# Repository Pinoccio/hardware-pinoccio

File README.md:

pinoccio-hardware-reference
===========================

Contained are the schematics, board layout, data sheets, and BOM for the
Pinoccio board. The firmware directory also has code for the 16u2 chip
on the board and the booloader running in the main MCU.

For the firmware, the branches contain only the source files. The
compiled versions used in production can be found in the tagged
revisions only.

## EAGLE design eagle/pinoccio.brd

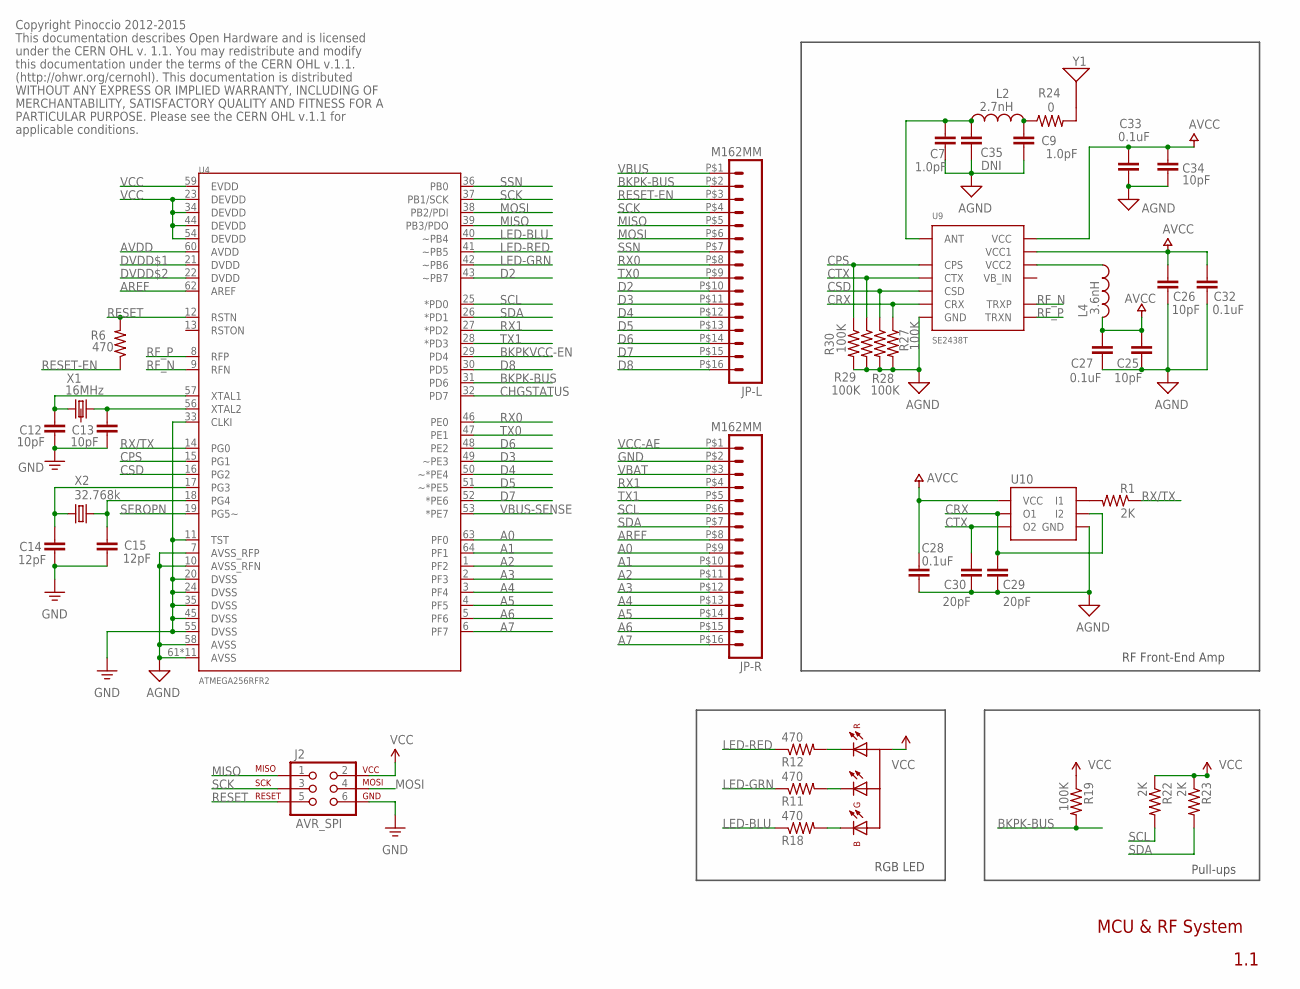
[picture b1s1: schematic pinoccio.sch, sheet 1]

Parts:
C7, C9: 1.0pF; 0402-CAP
C12, C13, C25, C26, C34: 10pF; 0402-CAP
C14, C15: 12pF; 0402-CAP
C27, C28, C32, C33: 0.1uF; 0402-CAP
C29, C30: 20pF; 0402-CAP
C35: DNI; 0402-CAP
J2: AVR_SPI; 2X3-PAD
JP-L: M162MM; 1X16_2MM
JP-R: M162MM; 1X16_2MM
L2: 2.7nH; 0402
L4: 3.6nH; 0402
R1, R22, R23: 2K; 0402-RES
R6, R11, R12, R18: 470; 0402-RES
R19, R27, R28, R29, R30: 100K; 0402-RES
R24: 0; 0402-RES
U4: ATMEGA256RFR2; QFN-64-256RFR2
U8: LED-RGB; PLCC4
U9: SE2438T; QFN-20-SE2438T
U10: INVERTER-DUALPAK; MICROPAK
X1: 16MHz; CRYSTAL-SMD-2.5X2-ABM10
X2: 32.768k; CRYSTAL-SMD-2X1.2-ABS06
Y1: ANTENNA2SMD5; ANTENNA-CHIP5

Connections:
A0: JP-R.P$9 (9), U4.63 (PF0)
A1: JP-R.P$10 (10), U4.64 (PF1)
A2: JP-R.P$11 (11), U4.1 (PF2)
A3: JP-R.P$12 (12), U4.2 (PF3)
A4: JP-R.P$13 (13), U4.3 (PF4)
A5: JP-R.P$14 (14), U4.4 (PF5)
A6: JP-R.P$15 (15), U4.5 (PF6)
A7: JP-R.P$16 (16), U4.6 (PF7)
ANT: C7.1, C35.1, L2.2, U9.13 (ANT)
AREF: JP-R.P$8 (8), U4.62 (AREF)
AVDD: U4.60 (AVDD); also elsewhere on the board
BKPK-BUS: JP-L.P$2 (2), R19.2, U4.31 (PD6)
BKPKVCC-EN: U4.29 (PD4); also elsewhere on the board
CHGSTATUS: U4.32 (PD7); also elsewhere on the board
CPS: R30.1, U4.15 (PG1), U9.8 (CPS)
CRX: C29.1, R27.1, U9.10 (CRX), U10.P$3 (I2), U10.P$6 (O1)
CSD: R28.1, U4.16 (PG2), U9.12 (CSD)
CTX: C30.1, R29.1, U9.11 (CTX), U10.P$4 (O2)
D2: JP-L.P$10 (10), U4.43 (~PB7)
D3: JP-L.P$11 (11), U4.49 (~PE3)
D4: JP-L.P$12 (12), U4.50 (~*PE4)
D5: JP-L.P$13 (13), U4.51 (~*PE5)
D6: JP-L.P$14 (14), U4.48 (PE2)
D7: JP-L.P$15 (15), U4.52 (*PE6)
D8: JP-L.P$16 (16), U4.30 (PD5)
DVDD$1: U4.21 (DVDD); also elsewhere on the board
DVDD$2: U4.22 (DVDD); also elsewhere on the board
GND: C7.2, C9.2, C12.2, C13.2, C14.2, C15.2, C25.2, C26.2, C27.2, C28.2, C29.2, C30.2, C32.2, C33.2, C34.2, C35.2, J2.6, JP-R.P$2 (2), R27.2, R28.2, R29.2, R30.2, U4.7 (AVSS_RFP), U4.10 (AVSS_RFN), U4.11 (TST), U4.20 (DVSS), U4.24 (DVSS), U4.33 (CLKI), U4.35 (DVSS), U4.45 (DVSS), U4.55 (DVSS), U4.58 (AVSS), U4.61 (AVSS), U4.GND$1 (AVSS), U4.GND$2 (AVSS), U4.GND$3 (AVSS), U4.GND$4 (AVSS), U4.GND$5 (AVSS), U4.GND$6 (AVSS), U4.GND$7 (AVSS), U4.GND$8 (AVSS), U4.GND$9 (AVSS), U4.PADDLE (AVSS), U9.5 (GND), U9.14 (GND), U9.18 (GND), U9.20 (GND), U9.EP (GND), U9.GND, U9.GND$1 (GND), U10.P$2 (GND); also elsewhere on the board
LED-BLU: R18.1, U4.40 (~PB4)
LED-GRN: R11.1, U4.42 (~PB6)
LED-RED: R12.1, U4.41 (~PB5)
MISO: J2.1, JP-L.P$5 (5), U4.39 (PB3/PDO)
MOSI: J2.4, JP-L.P$6 (6), U4.38 (PB2/PDI)
unnamed: R12.2, U8.P$1 (R-C)
unnamed: L4.2, U9.19 (VCC2)
unnamed: R11.2, U8.P$4 (G-C)
unnamed: R18.2, U8.P$3 (B-C)
unnamed: R1.2, U10.P$1 (I1)
unnamed: C14.1, U4.17 (PG3), X2.P$1 (1)
unnamed: C15.1, U4.18 (PG4), X2.P$2 (2)
unnamed: C9.1, L2.1, R24.1
unnamed: R24.2, Y1.FEED
RESET: J2.5, R6.2, U4.12 (RSTN); also elsewhere on the board
RESET-EN: JP-L.P$3 (3), R6.1
RF_N: U4.9 (RFN), U9.3 (TRXP)
RF_P: U4.8 (RFP), U9.4 (TRXN)
RX0: JP-L.P$8 (8), U4.46 (PE0); also elsewhere on the board
RX1: JP-R.P$4 (4), U4.27 (*PD2)
RX/TX: R1.1, U4.14 (PG0)
SCK: J2.3, JP-L.P$4 (4), U4.37 (PB1/SCK)
SCL: JP-R.P$6 (6), R22.2, U4.25 (*PD0); also elsewhere on the board
SDA: JP-R.P$7 (7), R23.2, U4.26 (*PD1); also elsewhere on the board
SEROPN: U4.19 (PG5~); also elsewhere on the board
SSN: JP-L.P$7 (7), U4.36 (PB0)
TX0: JP-L.P$9 (9), U4.47 (PE1); also elsewhere on the board
TX1: JP-R.P$5 (5), U4.28 (*PD3)
VBAT: JP-R.P$3 (3); also elsewhere on the board
VBUS: JP-L.P$1 (1); also elsewhere on the board
VBUS-SENSE: U4.53 (*PE7); also elsewhere on the board
VCC: C25.1, C26.1, C27.1, C28.1, C32.1, C33.1, C34.1, J2.2, L4.1, R19.1, R22.1, R23.1, U4.23 (DEVDD), U4.34 (DEVDD), U4.44 (DEVDD), U4.54 (DEVDD), U4.59 (EVDD), U8.P$2 (A), U9.1 (VCC1), U9.6 (VCC), U10.P$5 (VCC); also elsewhere on the board
VCC-AE: JP-R.P$1 (1); also elsewhere on the board
X1_N: C13.1, U4.56 (XTAL2), X1.P$3 (2)
X1_P: C12.1, U4.57 (XTAL1), X1.P$1 (1)

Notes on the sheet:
1.1
Copyright Pinoccio 2012-2015
This documentation describes Open Hardware and is licensed
under the CERN OHL v. 1.1. You may redistribute and modify
this documentation under the terms of the CERN OHL v.1.1.
(http://ohwr.org/cernohl). This documentation is distributed
WITHOUT ANY EXPRESS OR IMPLIED WARRANTY, INCLUDING OF
MERCHANTABILITY, SATISFACTORY QUALITY AND FITNESS FOR A
PARTICULAR PURPOSE. Please see the CERN OHL v.1.1 for
applicable conditions.
MCU & RF System
Pull-ups
RF Front-End Amp
RGB LED

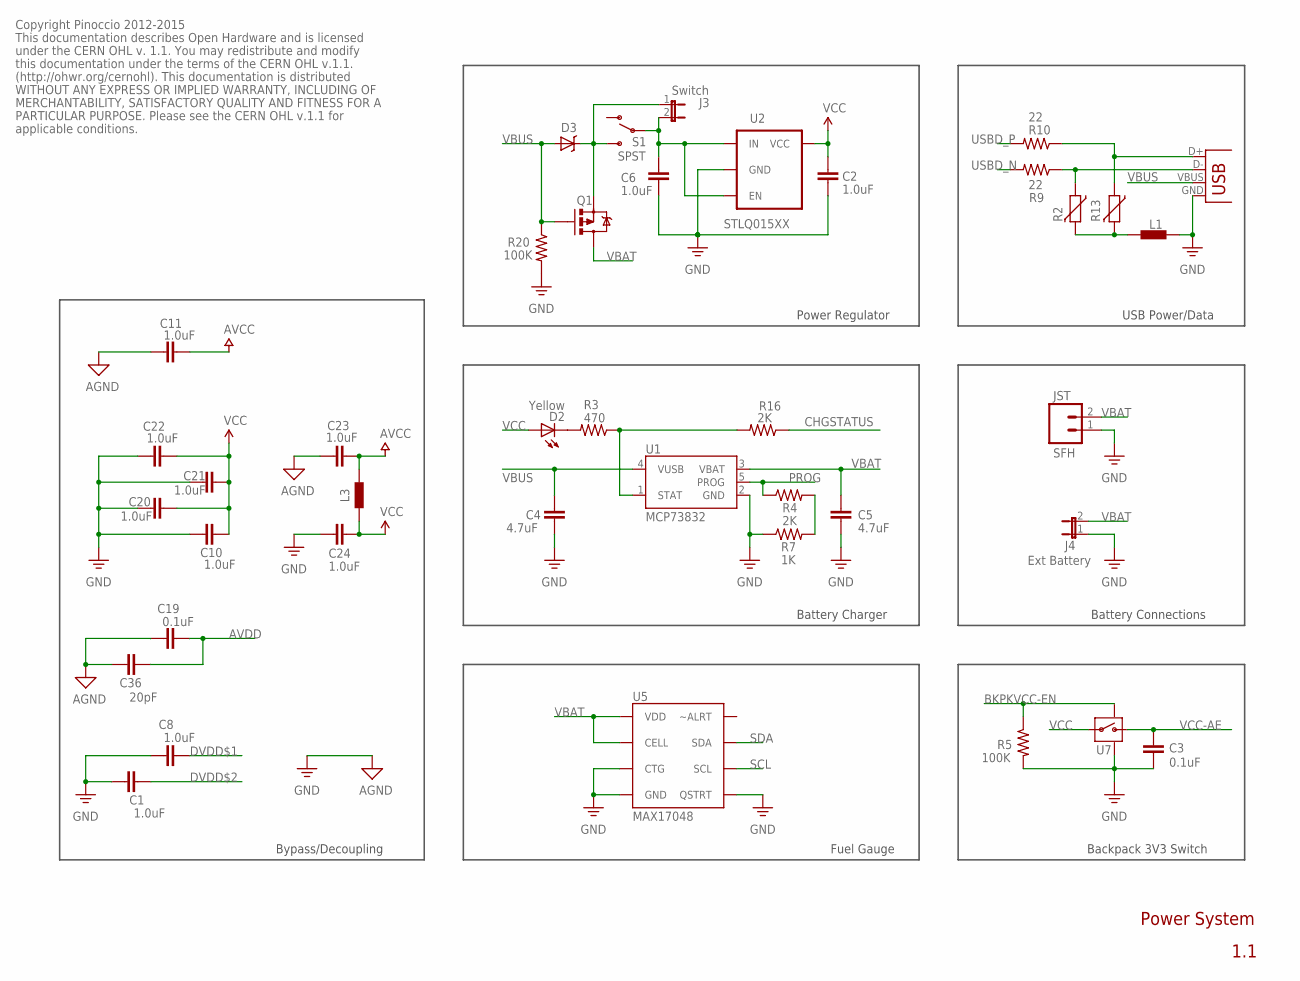
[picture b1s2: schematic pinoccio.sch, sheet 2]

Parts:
C1, C2, C6, C8, C10, C11, C20, C21, C22, C23, C24: 1.0uF; 0402-CAP
C3, C19: 0.1uF; 0402-CAP
C4, C5: 4.7uF; 0402-CAP
C36: 20pF; 0402-CAP
D2: Yellow; LED-0603
D3: DIODE-SCHOTTKY; 0603-DIODE
J3: Switch; 1X02
J4: Ext Battery; 1X02
JST: SFH; JST-SFH
L1, L3: BEAD; 0603
Q1: PFET; SOT23-3
R2, R13: VAR; 0402
R3: 470; 0402-RES
R4, R16: 2K; 0402-RES
R5, R20: 100K; 0402-RES
R7: 1K; 0402-RES
R9, R10: 22; 0402-RES
S1: SPST; SWITCH-SPDT-SMD
U1: MCP73832; SOT23-5
U2: STLQ015XX; SOT666
U5: MAX17048; DFN-8
U7: SWITCH; TDFN4
USB-JACK: USB-MICROB

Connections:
AVDD: C19.1, C36.1; also elsewhere on the board
BKPKVCC-EN: R5.1, U7.P$4 (ON); also elsewhere on the board
CHGSTATUS: R16.1; also elsewhere on the board
DVDD$1: C8.1; also elsewhere on the board
DVDD$2: C1.1; also elsewhere on the board
GND: C1.2, C2.2, C3.2, C4.2, C5.2, C6.2, C8.2, C10.2, C11.2, C19.2, C20.2, C21.2, C22.2, C23.2, C24.2, C36.2, J4.1, JST.1, L1.1, R5.2, R7.1, R20.2, U1.2 (GND), U2.P$2 (GND), U5.P$1 (CTG), U5.P$4 (GND), U5.P$6 (QSTRT), U5.P$9 (GND), U7.P$2 (GND), U7.P$5 (GND), USB-JACK.GND; also elsewhere on the board
unnamed: R4.2, R7.2
unnamed: L1.2, R2.2, R13.2
unnamed: R3.1, R16.2, U1.1 (STAT)
unnamed: D2.C, R3.2
unnamed: D3.C, J3.1, Q1.2 (S), S1.3 (S)
PROG: R4.1, U1.5 (PROG); also elsewhere on the board
SCL: U5.P$7 (SCL); also elsewhere on the board
SDA: U5.P$8 (SDA); also elsewhere on the board
USBDIN_N: R2.1, R9.1, USB-JACK.D-
USBDIN_P: R10.1, R13.1, USB-JACK.D+
USBD_N: R9.2; also elsewhere on the board
USBD_P: R10.2; also elsewhere on the board
VBAT: C5.1, J4.2, JST.2, Q1.3 (D), U1.3 (VBAT), U5.P$2 (CELL), U5.P$3 (VDD); also elsewhere on the board
VBUS: C4.1, D3.A, Q1.1 (G), R20.1, U1.4 (VUSB), USB-JACK.VBUS; also elsewhere on the board
VCC: C2.1, C10.1, C11.1, C20.1, C21.1, C22.1, C23.1, C24.1, D2.A, L3.1, L3.2, U2.P$4 (VCC), U7.P$3 (IN); also elsewhere on the board
VCC-AE: C3.1, U7.P$1 (OUT); also elsewhere on the board
VIN: C6.1, J3.2, S1.2, U2.P$1 (EN), U2.P$3 (IN)

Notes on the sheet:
1.1
Power Regulator
Battery Charger
Fuel Gauge
Bypass/Decoupling
USB Power/Data
Battery Connections
Backpack 3V3 Switch
Power System
Copyright Pinoccio 2012-2015
This documentation describes Open Hardware and is licensed
under the CERN OHL v. 1.1. You may redistribute and modify
this documentation under the terms of the CERN OHL v.1.1.
(http://ohwr.org/cernohl). This documentation is distributed
WITHOUT ANY EXPRESS OR IMPLIED WARRANTY, INCLUDING OF
MERCHANTABILITY, SATISFACTORY QUALITY AND FITNESS FOR A
PARTICULAR PURPOSE. Please see the CERN OHL v.1.1 for
applicable conditions.

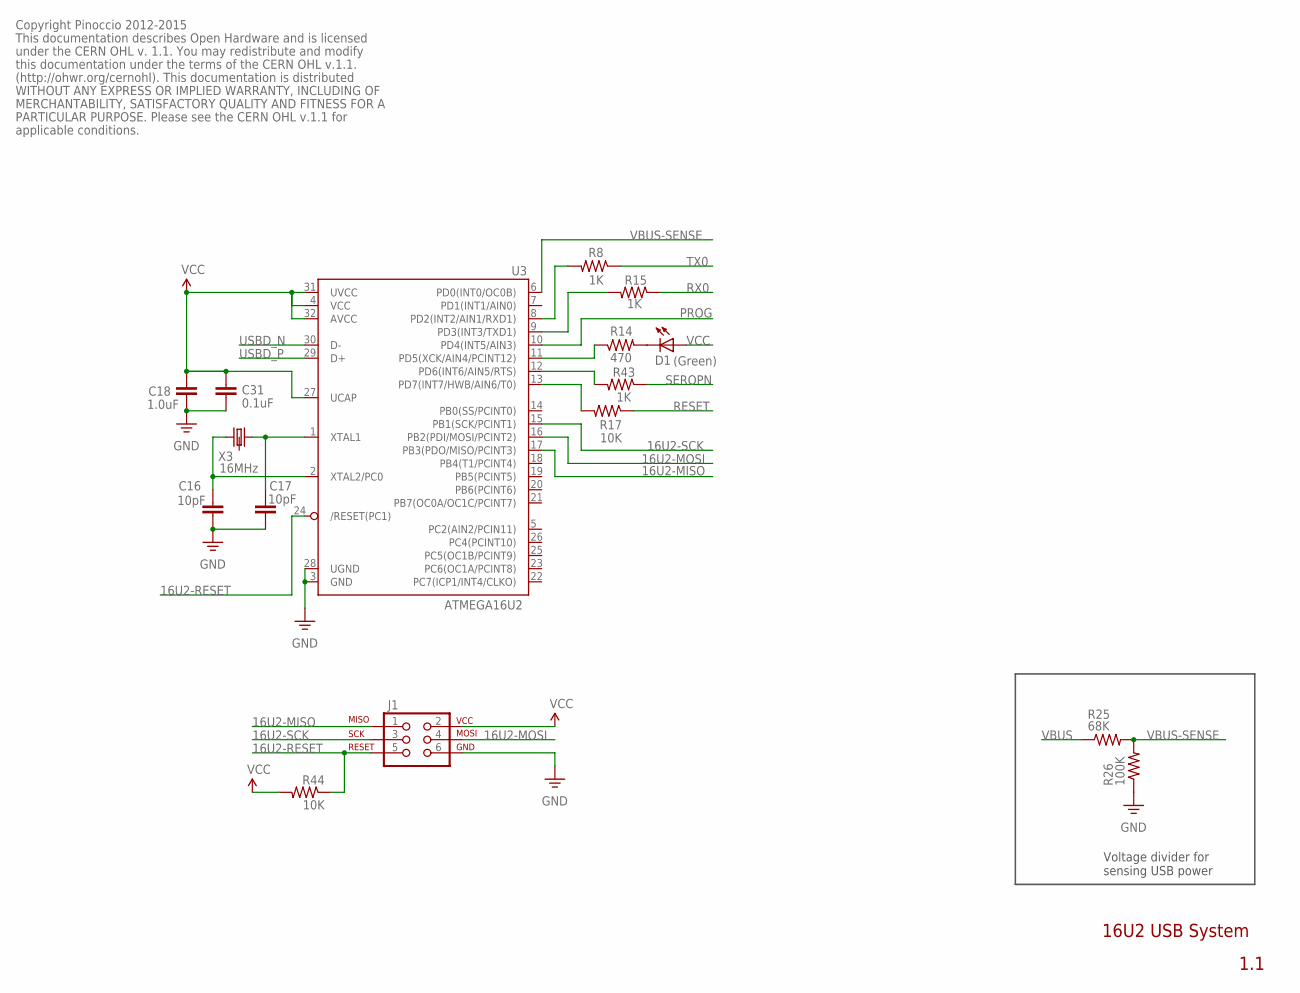
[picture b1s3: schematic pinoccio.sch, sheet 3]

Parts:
C16, C17: 10pF; 0402-CAP
C18: 1.0uF; 0402-CAP
C31: 0.1uF; 0402-CAP
D1: (Green); LED-0603
J1: AVR_SPI_PRG_6; 2X3-PAD
R8, R15, R43: 1K; 0402-RES
R14: 470; 0402-RES
R17, R44: 10K; 0402-RES
R25: 68K; 0402-RES
R26: 100K; 0402-RES
U3: ATMEGA16U2; QFN-32
X3: 16MHz; CRYSTAL-SMD-2.5X2-ABM10

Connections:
16U2-MISO: J1.1, U3.17 (PB3(PDO/MISO/PCINT3))
16U2-MOSI: J1.4, U3.16 (PB2(PDI/MOSI/PCINT2))
16U2-RESET: J1.5, R44.1, U3.24 (/RESET(PC1))
16U2-SCK: J1.3, U3.15 (PB1(SCK/PCINT1))
GND: C16.2, C17.2, C18.2, C31.2, J1.6, R26.1, U3.3 (GND), U3.28 (UGND); also elsewhere on the board
unnamed: R43.2, U3.12 (PD6(INT6/AIN5/RTS))
unnamed: R17.2, U3.13 (PD7(INT7/HWB/AIN6/T0))
unnamed: R15.2, U3.9 (PD3(INT3/TXD1))
unnamed: R8.2, U3.8 (PD2(INT2/AIN1/RXD1))
unnamed: R14.1, U3.11 (PD5(XCK/AIN4/PCINT12))
unnamed: D1.C, R14.2
PROG: U3.10 (PD4(INT5/AIN3)); also elsewhere on the board
RESET: R17.1; also elsewhere on the board
RX0: R15.1; also elsewhere on the board
SEROPN: R43.1; also elsewhere on the board
TX0: R8.1; also elsewhere on the board
USBD_N: U3.30 (D-); also elsewhere on the board
USBD_P: U3.29 (D+); also elsewhere on the board
VBUS: R25.1; also elsewhere on the board
VBUS-SENSE: R25.2, R26.2, U3.6 (PD0(INT0/OC0B)); also elsewhere on the board
VCC: C18.1, C31.1, D1.A, J1.2, R44.2, U3.4 (VCC), U3.27 (UCAP), U3.31 (UVCC), U3.32 (AVCC); also elsewhere on the board
X3_N: C16.1, U3.2 (XTAL2/PC0), X3.P$1 (1)
X3_P: C17.1, U3.1 (XTAL1), X3.P$3 (2)

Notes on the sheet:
1.1
16U2 USB System
Voltage divider for sensing USB power
Copyright Pinoccio 2012-2015
This documentation describes Open Hardware and is licensed
under the CERN OHL v. 1.1. You may redistribute and modify
this documentation under the terms of the CERN OHL v.1.1.
(http://ohwr.org/cernohl). This documentation is distributed
WITHOUT ANY EXPRESS OR IMPLIED WARRANTY, INCLUDING OF
MERCHANTABILITY, SATISFACTORY QUALITY AND FITNESS FOR A
PARTICULAR PURPOSE. Please see the CERN OHL v.1.1 for
applicable conditions.

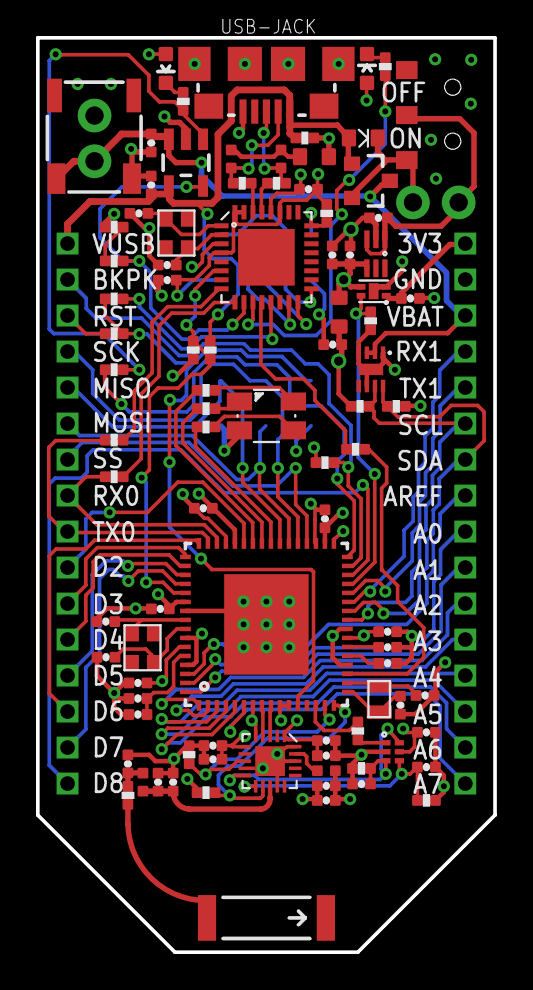
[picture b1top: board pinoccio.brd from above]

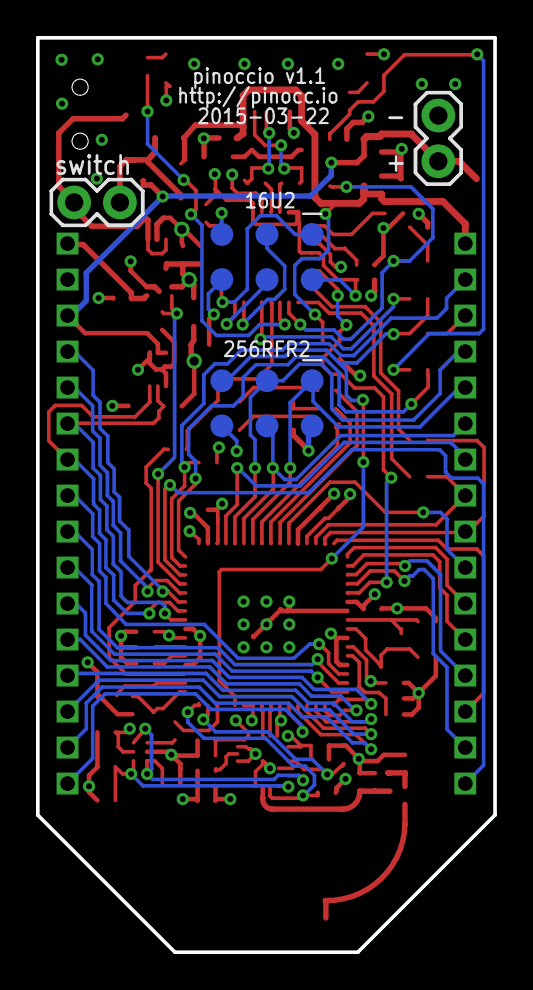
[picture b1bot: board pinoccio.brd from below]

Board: 4 copper layers, 25.4 x 50.8 mm, 97 parts (4 on the bottom side), 86 nets.

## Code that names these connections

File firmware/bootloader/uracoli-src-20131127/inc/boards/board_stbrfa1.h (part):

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<pre>
RCB2xx        | Pin           | RCB128RFA1   | Remark
------------------------------------------------------------------
PA0             EXT1.23         PB0          \
PA1             EXT1.24         PB1          |  This is the
PA2             EXT1.25         PB2          |  multiplexed
PA3             EXT1.26         PB3          >  data/low address
PA4             EXT1.27         PB4          |  bus of the classic
PA5             EXT1.28         PB5          |  XMEM interface
PA6             EXT1.29         PB6          |
PA7             EXT1.30         PB7          /
PE4             EXT1.6          RSTON        Reset output
PE5             EXT1.5          TST          Used for "HV" prog
PC4             EXT0.25         PD4          \  Matches A12...A15
PC5             EXT0.26         PD5          |  of normal address bus;
PC6             EXT0.27         PD6          >  used to distinguish
PC7             EXT0.28         PD7          /  FTDI vs. LED vs. button
PG0             EXT0.17         PE4          xmem /WR
PG1             EXT0.18         PE5          xmem /RD
PB6             EXT0.1          PG0          GPIO
PB7             EXT0.2          PG1          GPIO
XTAL1           EXT0.7          CLKI
</pre>
    In addition, the standard STB pin mapping is retained for:

    PE7  FT245 /RXF
    PE6  FT245 /TXE
    PG2  ALE

    The STBxxx has memory mapped LEDS and Keys.
    KEY: memory mapped on external memory bus address 0x4000
    LEDS
     - 2 x memory mapped at 0x4000  (Option 1)
     - 3 x IO mapped at PE2:PE4 (Option 2)


    You can select between using the LEDs on the RCB or on the STB.
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    DDRD |= 0xc0;               /* xmem A14...A15 */
    PORTD = (PORTD & ~0xc0) | 0x80; /* high addr 0x80 => external
                                     * SRAM */
    PORTE &= ~0x10;             /* PE4: xmem /WR, activate to make the
                                 * 74VHC245MTC not drive the bus */
    PORTE |= 0x20;              /* PE5: xmem /RD, deactivate */
    DDRE |= 0x30;               /* make /RD and /WR outputs */
    PORTG &= ~0x04;             /* PG2: xmem ALE; not used but keep
                                 * low all the time */
    DDRG |= 0x04;
}
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
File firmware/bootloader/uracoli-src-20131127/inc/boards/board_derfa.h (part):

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

radiofaro:
  LEDS: PG1, PG2

</pre>

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
#define LED_INIT() \
    do {\
        DDRB |= (_BV(PB0) | _BV(PB1) | _BV(PB2) | _BV(PB3));\
        PORTB |= (_BV(PB0) | _BV(PB1) | _BV(PB2) | _BV(PB3));\
    } while(0)


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#if BOARD_TYPE == BOARD_DERFN128

    /*
     * USBRD = Pin27 = PD2
     * USBWR = Pin10 = PD3
     * RXF   = Pin30 = PE2
     * TXE   = Pin21 = PB5
     * Data Port:
     * D0 =  Pin16 = PB0
     * D1 =  Pin41 = PF2
     * D2 =  Pin12 = PD5
     * D3 =  Pin06 = PG2
     * D4 =  Pin37 = PE6
     * D5 =  Pin19 = PB4
     * D6 =  Pin39 = PE7
     * D7 =  Pin18 = PB6
     */

    static inline void hif_mmio_init(void)
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        DDRD |= 0xc0;               /* xmem A14...A15 */
        PORTD = (PORTD & ~0xc0) | 0x80; /* high addr 0x80 => external
                                         * SRAM */
        PORTE &= ~0x10;             /* PE4: xmem /WR, activate to make the
                                     * 74VHC245MTC not drive the bus */
        PORTE |= 0x20;              /* PE5: xmem /RD, deactivate */
        DDRE |= 0x30;               /* make /RD and /WR outputs */
        PORTG &= ~0x04;             /* PG2: xmem ALE; not used but keep
                                     * low all the time */
        DDRG |= 0x04;
    }
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
# define TRX_PA_LNA_INIT() \
        do {\
            PORTD &= ~_BV(PD6);\
            DDRD |= _BV(PD6);\
        } while(0)

# define TRX_TX_PA_EI() do {PORTD |= _BV(PD6);} while(0)
# define TRX_TX_PA_DI() do {PORTD &= ~_BV(PD6);} while(0)
# define TRX_RX_LNA_EI() do {PORTD |= _BV(PD6);} while(0)
# define TRX_RX_LNA_DI() do {PORTD &= ~_BV(PD6);} while(0)
#endif /* BOARD_TYPE == BOARD_RASPBEE || BOARD_TYPE == BOARD_DERFN256U0PA || BOARD_TYPE == BOARD_DERFN128U0 */


#if BOARD_TYPE == BOARD_DERFN128U0 || BOARD_TYPE == BOARD_DERFN128
#define I2C_ENABLE() do{\
        DDRD |= (1<<PD6);\
        PORTD &= ~(1<<PD6);\
    }while(0)

#define ISL29020_ADDR (0x44)
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
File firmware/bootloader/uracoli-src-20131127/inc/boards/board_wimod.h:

/* Copyright (c) 2007 - 2011 Axel Wachtler
   All rights reserved.

   Redistribution and use in source and binary forms, with or without
   modification, are permitted provided that the following conditions
   are met:

   * Redistributions of source code must retain the above copyright
     notice, this list of conditions and the following disclaimer.
   * Redistributions in binary form must reproduce the above copyright
     notice, this list of conditions and the following disclaimer in the
     documentation and/or other materials provided with the distribution.
   * Neither the name of the authors nor the names of its contributors
     may be used to endorse or promote products derived from this software
     without specific prior written permission.

   THIS SOFTWARE IS PROVIDED BY THE COPYRIGHT HOLDERS AND CONTRIBUTORS "AS IS"
   AND ANY EXPRESS OR IMPLIED WARRANTIES, INCLUDING, BUT NOT LIMITED TO, THE
   IMPLIED WARRANTIES OF MERCHANTABILITY AND FITNESS FOR A PARTICULAR PURPOSE
   ARE DISCLAIMED. IN NO EVENT SHALL THE COPYRIGHT OWNER OR CONTRIBUTORS BE
   LIABLE FOR ANY DIRECT, INDIRECT, INCIDENTAL, SPECIAL, EXEMPLARY, OR
   CONSEQUENTIAL DAMAGES (INCLUDING, BUT NOT LIMITED TO, PROCUREMENT OF
   SUBSTITUTE GOODS OR SERVICES; LOSS OF USE, DATA, OR PROFITS; OR BUSINESS
   INTERRUPTION) HOWEVER CAUSED AND ON ANY THEORY OF LIABILITY, WHETHER IN
   CONTRACT, STRICT LIABILITY, OR TORT (INCLUDING NEGLIGENCE OR OTHERWISE)
   ARISING IN ANY WAY OUT OF THE USE OF THIS SOFTWARE, EVEN IF ADVISED OF THE
   POSSIBILITY OF SUCH DAMAGE. */

/* $Id$ */
/**
 * @file
 * @brief IMST GmbH WIMOD w/ mega328 and AT86RF230B.
 *
 * see http://www.mikrocontroller.net/attachment/101618/WiMOD240.jpg

 * The wiring of the radio and the ATmega is shown below.
<pre>
     AVR         RF230
     ---         -----
     PB0    <--  INT / ICP1
     PB1    -->  SLPTR
     PB2    -->  /SEL
     PB3    -->  MOSI
     PB4    <--  MISO
     PB5    -->  SCK

     PB6 intentionally unused for XTAL1
     PB7 intentionally unused for XTAL2


    (T1) PD5   <--  CLKM
         PD6   --> /RST
         PD7   --> TST

    USART:
        PD0 RXD
        PD1 TXD

    LED:  None
    KEY:  None


  IM240A      Mega328  Adapter   EvalBoard
  Pin Name              AB_01
  -----------------------------------------
   8  ADC1    ADC7      X1.12
   9  ADC2    ADC6      X1.14
  12  GPIO1   PC0       X1.15     Button1
  13  GPIO2   PC1       X1.16     Button2
  14  GPIO3   PC2       X1.19     Button3
  15  GPIO4   PC3       X1.18     DSW1
  21  GPIO5   PC5       X2.9
  23  GPIO6   PC4       X2.11

  18  DIO1    PD0       X2.18      UART-RX
  19  DIO2    PD1       X2.15      UART-TX
  20  DIO3    PD2       X2.7       LED4
  24  DIO4    PD3       X2.6       LED3
  25  DIO5    PD4       X2.5       LED2

</pre>

  @par Build Options

 - im240a : AT86RF230B w/ mega328.
 - im240a_eval : AT86RF230B w/ mega328 eval board.

 @note
  In order to use the eval board be shure to follow the install guide.
   - replace jumper e by cable e1 on X5
   - switch S1 to power supply USB.

   To program the mega328pa connect JTAG-ICE 10 pin header to X4.

   avrdude -P usb -c jtag2isp -p m328p -B10 -t

   The original fuses are
   LF 0xe2
   HF 0xd4
   EF 0x06


   The original bootloader seems to be a proprietary one and handles
   the ISMT *.wfi format. It is a one line string starting with
   "WIMOD_ID_3#" followed by probably the ASCII representation
   of the firmware ... to be investigated.

   In order to do a backup of the board use the following commands:
   <pre>
    avrdude -P usb -c jtag2isp -p m328p -B 10 -U fl:r:im240a_flash_initial.hex:i
    avrdude -P usb -c jtag2isp -p m328p -B 10 -U ee:r:im240a_eeprom_initial.hex:i
   </pre>

  Restoration of the backup can be done by the command:
  <pre>
  avrdude -P usb -c jtag2isp -p m328p -B 10 \
            -U fl:w:im240a_flash_initial.hex:i \
            -U ee:w:im240a_eeprom_initial.hex:i \
            -U lf:w:0xe2:m \
            -U hf:w:0xd4:m \
            -U ef:w:0x06:m
    </pre>
 */


#ifndef BOARD_WIMOD_H
#define BOARD_WIMOD_H (1)
#if defined(im240a)
# define BOARD_NAME "im240a"
# define BOARD_TYPE BOARD_IM240A
#elif defined(im240a_eval)
# define BOARD_NAME "im240a_eval"
# define BOARD_TYPE BOARD_IM240A_EVAL
#endif
/*=== Compile time parameters ========================================*/
#ifndef DEFAULT_SPI_RATE
# define DEFAULT_SPI_RATE  (SPI_RATE_1_2)
#endif

/*=== Hardware Components ============================================*/
#define RADIO_TYPE (RADIO_AT86RF230B)

/*=== TRX pin access macros ==========================================*/

#define DDR_TRX_RESET   DDRD
#define PORT_TRX_RESET  PORTD
#define MASK_TRX_RESET  (_BV(PD6))
#define TRX_RESET_INIT() DDR_TRX_RESET |= MASK_TRX_RESET
#define TRX_RESET_HIGH() PORT_TRX_RESET |= MASK_TRX_RESET
#define TRX_RESET_LOW()  PORT_TRX_RESET &= ~MASK_TRX_RESET

#define PORT_TRX_SLPTR  PORTB
#define DDR_TRX_SLPTR   DDRB
#define MASK_TRX_SLPTR  (_BV(PB1))

#define TRX_SLPTR_INIT() DDR_TRX_SLPTR |= MASK_TRX_SLPTR
#define TRX_SLPTR_HIGH() PORT_TRX_SLPTR |= MASK_TRX_SLPTR
#define TRX_SLPTR_LOW()  PORT_TRX_SLPTR &= ~MASK_TRX_SLPTR


/*=== IRQ access macros ==============================================*/
# define TRX_IRQ_vect    TIMER1_CAPT_vect    /**< interrupt vector name */

/** init interrupt handling
 *  - transceiver IRQ at PB0
 *  - rising edge triggers ICP1 (ICES1),
 *  - timer capture is enabled (ICF1)

 */
# define TRX_IRQ_INIT()  do{\
                            /* TCCR1B |= (_BV(ICNC1) | _BV(ICES1) | _BV(CS12) | _BV(CS10)); */\
                            TCCR1B |= (_BV(ICNC1) | _BV(ICES1));\
                            TIFR1 = _BV(ICF1);\
                          } while(0)

/** disable TRX interrupt */
#define DI_TRX_IRQ() {TIMSK1 &= ~_BV(ICIE1);}

/** enable TRX interrupt */
#define EI_TRX_IRQ() {TIMSK1 |= _BV(ICIE1);}

/** timestamp register for RX_START event */
#define TRX_TSTAMP_REG TCNT1
/*=== SPI access macros ==============================================*/
#define DDR_SPI  (DDRB)
#define PORT_SPI (PORTB)

#define SPI_MOSI _BV(PB3)
#define SPI_MISO _BV(PB4)
#define SPI_SCK  _BV(PB5)
#define SPI_SS   _BV(PB2)

#define SPI_DATA_REG SPDR

static inline void SPI_INIT(uint8_t spirate)
{
    /* first configure SPI Port, then SPCR */
    PORT_SPI |= SPI_SCK | SPI_SS;
    DDR_SPI  |= SPI_MOSI | SPI_SCK | SPI_SS;
    DDR_SPI  &= ~SPI_MISO;

    SPCR = (_BV(SPE) | _BV(MSTR));

    SPCR &= ~(_BV(SPR1) | _BV(SPR0) );
    SPSR &= ~_BV(SPI2X);

    SPCR |= (spirate & 0x03);
    SPSR |= ((spirate >> 2) & 0x01);

}

#define SPI_SELN_LOW()       uint8_t sreg = SREG; cli(); PORT_SPI &=~SPI_SS
#define SPI_SELN_HIGH()      PORT_SPI |= SPI_SS; SREG = sreg
#define SPI_WAITFOR()        do { while((SPSR & _BV(SPIF)) == 0);} while(0)

/*=== LED access macros ==============================================*/
#if (BOARD_TYPE == BOARD_IM240A_EVAL)
/* need to implement bit reversed LED mapping,
 * Current Usage
 * LSB : LED4, LSB+1 : LED3, MSB : LED2
 */
# define LED_PORT      PORTD
# define LED_DDR       DDRD
# define LED_MASK      (0x1c)
# define LED_SHIFT     (2)
# define LED_NUMBER    (3)
# define LEDS_INVERSE  (1)
#else
# define NO_LEDS       (1)
#endif

/*=== KEY access macros ==============================================*/
#if (BOARD_TYPE == BOARD_IM240A_EVAL)
# define PORT_KEY      PORTC
# define PIN_KEY       PINC
# define DDR_KEY       DDRC
# define MASK_KEY      (0x07)
# define SHIFT_KEY     (0)
# define INVERSE_KEYS  (1)
# define PULLUP_KEYS   (1)
#else
# define NO_KEYS       (1)
#endif


/*=== Host Interface ================================================*/
#define HIF_TYPE    HIF_UART_0


/*=== TIMER Interface ===============================================*/
/**
 * Mode: normal
 * Prescaler: 1
 * Overflow: 0xFFFFUL
 */
#define HWTMR_PRESCALE  (1)
#define HWTIMER_TICK    ((1.0*HWTMR_PRESCALE)/F_CPU)
#define HWTIMER_TICK_NB (0xFFFFUL)
#define HWTIMER_REG     (TCNT1)
#define TIMER_TICK      (HWTIMER_TICK_NB * HWTIMER_TICK)
#define TIMER_POOL_SIZE (4)
#define TIMER_INIT() \
    do{ \
        TCCR1B |= (_BV(CS10)); \
        TIMSK1 |= _BV(TOIE1); \
    }while(0)
# define TIMER_IRQ_vect   TIMER1_OVF_vect

#endif /* BOARD_WIMOD_H */

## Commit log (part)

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2012-10-04 Initial import
2012-10-04 Removed old datasheet
2012-10-04 Add OHL license info
2012-10-04 Update licensing on eagle files
2012-10-04 Add back hidden layers
2012-10-04 Updated description on board file
2012-10-04 Removed D1 LED for power--for better power handling. Instead, will modify the bootloader to flash the bicolor LED a couple times upon power up, then turn off. Thanks Louis for the idea!
2012-10-05 Add a couple more ground vias to minimize impedance
2012-10-05 Updated bicolor LED values to a more sane value. Add 0603 landing pattern for Lipo IC charge current capacity (for people to mod if they want higher C-ratings). Fix mosfet reversal error. (Thanks Mon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
2012-10-05 Updated datasheet to dual package transistor.
2012-10-08 Update package for right-angle switch, make minor changes as recommended in Atmel App Note AVR2044
2012-10-08 Moar ground routing/vias to decrease any possible inductance
2012-10-09 Updated pinoccio copper/mask logo
2012-10-30 Add addl. datasheets
2012-11-03 Updated rfa1 with PWM and interrupt notes
2012-11-07 More board updates
2012-11-28 more cleanups
2012-12-05 Updated to v0.7
2012-12-15 Update to v0.9 for lower power regulator, replace MOSFET with dual switch, and other cleanups
2012-12-17 Change up header socket pins for better scatter cable adapter support
2012-12-18 Fix up more minor tweaks
2012-12-24 Clean up extra lines
2012-12-26 Fix changes needed for reset pullup resistor for 16U2
2012-12-26 Update changes file
2012-12-28 re-cleaned up reset line to 16U2
2012-12-28 update phone number in docs
2013-01-01 Moar fixups
2013-01-03 Fix up library naming
2013-01-04 move charge LED anode side to vbat instead of vusb
2013-01-04 Adjust a couple of spacing issues
2013-01-07 More minor silkscreen updates
2013-01-16 Tagging for v0.9
2013-03-30 v0.10 update
2013-04-01 Add addl contributors, and swap dual load switch for single load switch
2013-04-01 updated changes.txt
2013-04-13 version 0.11 updates
2013-04-26 current
2013-04-26 Fix wrong value for pull-down on mosfet
2013-07-07 v0.12 changes
2013-07-10 Add v0.12 pdfs
2013-07-12 Add resistor change to pulldown
2013-07-13 version 0.13
2013-07-16 v0.13 changes
2013-07-16 Minor schematic tweak
2013-07-19 update pi network components
2013-09-24 updated names of components for assembly
2013-11-20 Remove 128RFA1 datasheet
2013-11-20 Updated PDF version of schematic
2014-02-26 Add atmega16u2 firmware
    This is the firmware that runs on the 16u2 that does USB->serial
    conversion on the Pinoccio Scout. This firmware was previously stored in
    the piniccio-firmware / core-pinoccio repository, but it is more at
    place here.
2014-07-03 Add BOM and labels for jumpers
2014-10-15 Add source for bootloader
    This copies the source from [the core-pinoccio][1] repository, with the
    following modifications:
    - All compiled versions have been left out (release_* and Debug
    directories).
    - The Atmel Studio project has been replaced by a Makefile (using the
    same compiler options).
2014-11-10 dissector: Add license and description
2014-11-13 dissector: Update the recent protocol version
    The dissector still assumed an early version of the protocol, which was
    changed somewhere during 2012. This updates the dissector to a newer
    version of the protocol.
    This makes the following changes:
    - Remove channel sweep packets
    - Add Wibo set target, deaf and set address commands
2014-11-13 dissector: Don't bother dissecting 802.15.4 fields
    Wireshark can already do this, so no need to have them displayed twice.
2014-11-13 dissector: Add helper function for P2P_XMPL_LED packets
    Before, the dissecting of this packet type happened right in the main
    dissector function, unlike all other packet types.
2014-11-13 dissector: Handle "Range is out of bounds" errors
    When a packet is shorter than expected, the tvb class raises this error.
    By splitting the main dissector function and using pcall, we can capture
    this error and add an appropriate expert info error message.
2014-11-13 dissector: Simplify parsing by using a sub-buffer
    The wireshark Tvb class allows creating virtual sub-buffers, so we can
    just pass a buffer with just the packet payload to the parsing
    functions, instead of the original buffer and an offset.
2014-11-13 dissector: Restructure parsing
    Instead of registering as a postdissector that gets run on all
    (complete) packets, we register as both a normal and heuristic
    dissector for wpan packets. This means we'll only get called for
    802.15.4 packets, that do not have a packet type manually set (using
    "Decode as...").
    This also means the buffer we get passed only contains the 802.15.4 data
2014-11-13 dissector: Simplify registration of ProtoFields
    Instead of creating them as a pile of local variables and adding them to
    p2p.fields later, just create them as members of p2p.fields directly.
    Apparently the Wireshark Lua bindings contain some magic to allow this.
2014-11-13 dissector: Add error message when packet is too long
2014-11-13 dissector: Remove some unused code
2014-11-13 dissector: Fix boardname length
    It was previously changed to take 16 characters, but it actually takes
    up the remainder of the packet.
2014-11-13 dissector: Add additional info to the packet summary line
2014-11-13 dissector: Fix heuristic return value
    It turns out calling p2p.dissector always returns nil, so the previous
    lambda workaround does not apply. Now we just keep the dissector
    function around as a normal function, so we can pass it to
    register_heuristic directly.
2014-11-17 bootloader: Work around gcc bug with -fno-jump-tables
2014-11-17 bootloader: More thorougly clean uracoli
2014-11-17 bootloader: Make debug output from wibo.c work
    Before, this tried to use some "hif" I/O abstraction, probably from
    uracoli, while main.c already set up the UART. This commit makes wibo.c
    use the sendchar function defined in main.c already.
    Debug output is disabled by default, it needs -D_DEBUG_SERIAL to be
    passed while compiling to work.
2014-11-17 bootloader: Don't dump full wibo packets
    Dumping a full packet takes so long that a sender is likely to send
    another packet while we're still dumping, causing us to miss the packet.
    This is only relevant when compiled with debug output enabled.
2014-12-12 Remove support for WIBO / OTA
2014-12-12 Remove serial monitor related code
2014-12-12 Remove unused STK500 commands
2014-12-12 Remove some (now) unused files
2014-12-16 Hardware updates to Scout v1.1
    - Add 10k pull-up to reset line (#7)
    - Add diode in parallel to 10k pull-up reset resistor (#6)
    - Tie second pad on 16U2 crystal to ground (was not connected before)
    - Replace LDO with lower-ripple alternative (#8) (STLQ015XX33)
    - Add ground tie (0Ω) to pin 2 of balun
    - Change all caps in RF signal path to RF-rated C0G/NPO (Murata GRM series)
2014-12-17 Add caps to FEM
2014-12-17 Change 256RFR2 decoupling to 0.1µF and add single 1.0µF for transient current draw
2014-12-29 Restore proper serial timeout
    Before, the timeout calculation relied on a division in the led code,
    that dominated the iteration time. With that code gone, the iteration
    time and thus the total timeout is way to short to work.
2014-12-31 Map all writes to second flash half
2014-12-31 Ignore address and size from serial
    Also, remove some EEPROM related code that was unused and optimized away
    already.
2014-12-31 Remove commands unrelated to bug
    These are not needed anymore when we use a custom python script to send
    jyust data commands instead of using avrdude.
2014-12-31 Fix data to write
    I had the endianness inverted
2014-12-31 Remove bootloader timeout handling and reply sending
2014-12-31 Simplify command structure, drop seqnum, token and checksum
2014-12-31 Remove more unused stuff
2014-12-31 Remove more stuff
2014-12-31 Remove boot_rww_enable, it seems this is also not essential in reproducing the bug
2014-12-31 Clean up last code into a minimal example
    - Write nops to make sure that a jump into the main application wraps
    around to the start of the bootloader again.
    - Add led and pin toggles to monitor progress.
    - Add led and pin toggle when bootloader starts without any MCUSR bits
    set.
2014-12-31 Remove command.h, no longer used
2014-12-31 Fix comments to keep github disassembly syntax highlighting happy
2015-01-02 Clean up labels and fix bypass/decoupling caps
2015-02-11 Remove some unneeded includes
2015-02-11 Update pinout for zigbit module
    This updates the pinout for the "ATmega256RFR2 ZigBit Xplained Pro
    Extension" (ATZB-256RFR2-XPRO-ND). It uses the green and yellow leds to
    indicate flashing progress, and the red led to indicate an invalid boot
    (no MCUSR bit set).
    Additionally, it uses the first 4 pins of J3 (PF0 - PF3) for logic
    analyzer output.
2015-03-06 bootloader: Add source
    This copies the source from [the core-pinoccio][1] repository, with the
    following modifications:
    - All compiled versions have been left out (release_* and Debug
    directories).
    - The Atmel Studio project has been replaced by a Makefile (using the
    same compiler options).
2015-03-06 16u2: Remove DFU-related stuff
    Since we're not using the DFU bootloader, better remove it. combine.sh
    is for combining the firmware with the bootloader and the readme also
    assumes DFU is used, which would only be confusing.
2015-03-06 16u2: Remove Arduino-usbserial-noreset.c
    This seems like it was a copy of an older version of Arduino-usbserial.c
    that is not used in the build, with autoreset disabled. Best clean it up
    to prevent confusion.
2015-03-06 Remove PDF versions of old schematic and board version
    Instead of keeping all PDF versions, we'll just add them for specific
    git tags.
2015-03-06 Update README for previous changes
2015-03-06 Add compiled 16u2 firmware and bootloader
    These are the versions that are used on the Pinoccio Scout v1.0 boards
    that have been shipped.
    The source of these .hex files is a bit fuzzy. It's not known what
    compiler versions were used exactly (the bootloader has been compiled
    before the makefile existed, so it was even compiled by two different
    compiler versions, one in Atmel Studio for the bootloader and one
2015-03-06 Remove colon from datasheet filename
    Turns out Windows doesn't like these filenames, so just use a space
    instead.
2015-03-06 bootloader: Go to sleep during SPM write operation
    Atmel confirms there is a hardware bug that can, under some unknown set
    of circumstances, overwrite the program counter when writing to the
    second half of the flash on the ATMEGA64/128/256 RFR2 and 4RFR2 family.
    As a workaround, it helps to sleep during the SPM operation (waiting for
    the SPM complete interrupt to wake us up), since the bug requires
    reads from flash to trigger.
2015-03-06 bootloader: Simplify spm_wait slightly
    This removes the boot_spm_busy check, which isn't really needed.
    spm_wait is always executed just after the start of an spm operation, so
    there shouldn't be any chance of it being done already.
    However, even if it does happen, the SPM interrupt seems to be a
    level-interrupt, so it continuously fires when enabled and no SPM
    instruction is currently busy. So at worst, we have one extra sleep
2015-03-14 add datasheets
2015-03-22 Finished prelim layout for v1.1!
2015-03-22 Tweaked a few more things--ground fill, bottom silkscreen, etc.
2015-03-23 Fixed some missing airwires, and tweaked some positions
2015-03-23 added clearance to some resistor/cap pairs for easier hand assembly
2015-04-06 Update layout
2015-04-17 bootloader: Go to sleep during SPM write operation
    Atmel confirms there is a hardware bug that can, under some unknown set
    of circumstances, overwrite the program counter when writing to the
    second half of the flash on the ATMEGA64/128/256 RFR2 and 4RFR2 family.
    As a workaround, it helps to sleep during the SPM operation (waiting for
    the SPM complete interrupt to wake us up), since the bug requires
    reads from flash to trigger.

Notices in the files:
firmware/bootloader/uracoli-src-20131127/inc/boards/board_derfa.h:
Copyright (c) 2009 - 2013 Daniel Thiele, Eric Gnoske, Axel Wachtler
All rights reserved.
firmware/bootloader/uracoli-src-20131127/inc/boards/board_stbrfa1.h:
Copyright (c) 2011 Joerg Wunsch
eagle/pinoccio.brd:
Licensed under CERN OHL v.1.1
